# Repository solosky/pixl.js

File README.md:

# Pixl.js

这是一个基于原版[Pixl.js](http://www.espruino.com/Pixl.js)的复刻版本，主要的功能是用来模拟Amiibo。

## 图片

## 文档

* [中文文档](docs/zh/README.md)
* [English Documentation](docs/en/README.md)
* [Italian Documentation](docs/it/README.md)

## Credits

* [FlipperZero Firmware](https://github.com/flipperdevices/flipperzero-firmware)
* [mlib](https://github.com/P-p-H-d/mlib)
* [TLSF](https://github.com/mattconte/tlsf)
* [cwalk](https://github.com/likle/cwalk)
* [SPIFFS](https://github.com/pellepl/spiffs)
* [ChameleonUltra](https://github.com/RfidResearchGroup/ChameleonUltra)
* [CH32V003-GameConsole](https://github.com/wagiminator/CH32V003-GameConsole)

## Contribution 

* 特别感谢 @Caleeeeeeeeeeeee 完善的Bootloader。
* 特别感谢 @白橙 制作的外壳。 
* 特别感谢 @impeeza 提供的文档翻译 。

## 讨论群

国内用户可以加入QQ群 109761876 进行交流。

## Office Channel

Where do you find the community?
* [Pixl.js community discord server](https://discord.gg/4mqeQwcAB2)

## 声明

本项目为开源项目，仅为学习研究用途，请勿用于商业用途。 <br />
Amiibo是任天堂的注册商标，NTAG21X为NXP的注册商标。

内置的Amiibo数据库来源分别如下：

* [amiiloop](https://download.amiloop.app/)
* [AmiiboAPI](https://www.amiiboapi.com/)

源代码没有包含任何有任天堂版权的资源（比如相关密钥，Amiibo原始数据等）。

# License

本项目基于GPL 2.0 License发布，使用请遵循License的约定。

* 如果对项目做了修改，需要把改后的源码发布出来
* 发布出来的源码必须要使用相同的License发布

## 提示 

Amiibo无限刷需要网上搜索key_retail.bin文件然后上传到到磁盘根目录后才能使用。

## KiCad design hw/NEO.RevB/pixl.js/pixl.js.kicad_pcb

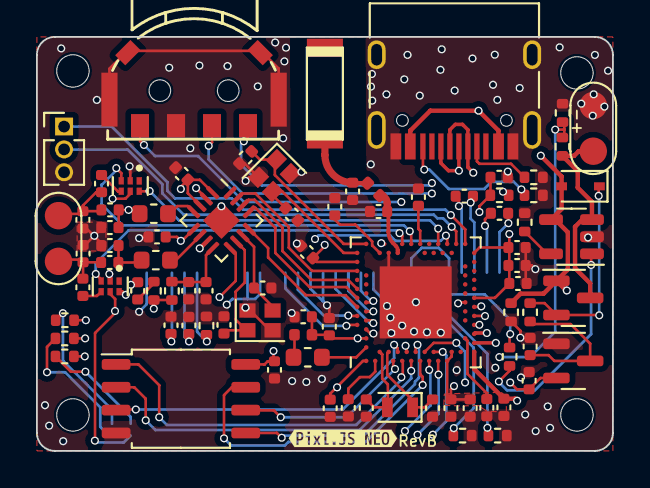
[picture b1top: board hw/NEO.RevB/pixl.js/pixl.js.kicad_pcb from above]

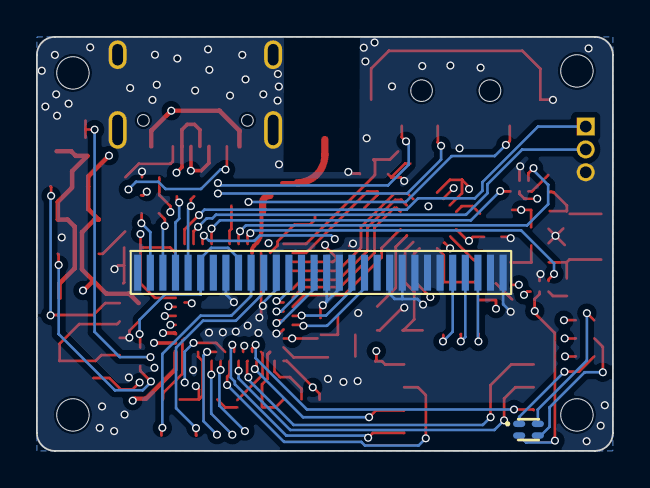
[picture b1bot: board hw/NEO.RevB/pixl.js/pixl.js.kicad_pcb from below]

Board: 4 copper layers, 32.0 x 23.0 mm, 90 parts (2 on the bottom side), 79 nets.

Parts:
BT1: LiPO; NFC_PAD
C1, C6, C13, C14, C17, C20, C24, C28, C30: 0.1uF; C_0402_1005Metric
C2, C5: TBD; C_0402_1005Metric
C3, C4: 15pF; C_0402_1005Metric
C7: 100pF; C_0402_1005Metric
C8, C10, C18, C19, C40: 4.7uF; C_0402_1005Metric
C9: 1nF; C_0402_1005Metric
C11, C21, C25, C29, C33, C36, C37, C42, C43: 1uF; C_0402_1005Metric
C12: 47nF; C_0402_1005Metric
C15, C16, C22, C23: 12pF; C_0402_1005Metric
C26, C27: 22pF; C_0402_1005Metric
C31, C32, C34, C35: 47pF; C_0402_1005Metric
C38, C39: 150pF; C_0402_1005Metric
C41: 2.2uF; C_0402_1005Metric
D1: LED_RGBA; LED-ARRAY-SMD_4P-L1.0-W1.0-TR-RD
D2: 1N5819; D_SOD-323
H1, H2, H3, H4: MountingHole; MountHole_D1.0mm_L10.0mm
J1: SWD; PinHeader_1x03_P1.27mm_Vertical
J2: Conn_01x30; FPC_30P_0.7
L1: TBD; L_0402_1005Metric
L2: 15nH; L_0402_1005Metric
L3: 10uH; L_0603_1608Metric
L4, L5: 2.2uH; L_0603_1608Metric
Q1: AO3401A; SOT-23
R1, R7, R8: 10K; R_0402_1005Metric
R2, R3, R11, R14: 5.1K; R_0402_1005Metric
R4, R5, R6: 1K; R_0402_1005Metric
R9: 806K; R_0402_1005Metric
R10: 2M; R_0402_1005Metric
R12: 100K; R_0402_1005Metric
R13: 0; R_0402_1005Metric
R15: 560K; R_0402_1005Metric
R16, R17: 4.7K; R_0402_1005Metric
U1: Antenna; AN2051
U2: USB_C_Receptacle_USB2.0; USB_C_Receptacle_HRO_TYPE-C-31-M-12
U3: 32MHz; Crystal_SMD_2016-4Pin_2.0x1.6mm
U4: nRF52840; Nordic_AQFN-73-1EP_7x7mm_P0.5mm
U5: 32.768kHz; Crystal_SMD_2012-2Pin_2.0x1.2mm
U6: CI522; QFN-16-1EP_3x3mm_P0.5mm_EP1.45x1.45mm
U7: 27.12MHz; Crystal_SMD_2016-4Pin_2.0x1.6mm
U8: W25Q32JVSS; SOIC-8_5.23x5.23mm_P1.27mm
U9: LTC4054-4.2; TSOT-23-5
U10, U11: 1G3157; PSON50P145X100X60-6N
U12: XC6206P332MR; SOT-23
U13: MSW
U14: NFC Antenna; NFC_PAD
kibuzzard-65881743: G***; kibuzzard-65881743

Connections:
+BATT: BT1.1 (+), Q1.3 (D), R9.1, U9.3 (BAT)
/BAT_ADC: R9.2, R10.1, U4.K2 (AIN3/P0.05)
/CHRG: R7.1, U4.P2 (P1.08), U9.1 (~CHRG)
/COIL_A: C26.1, C34.2, C38.1, U14.1
/COIL_B: C27.1, C35.2, C39.2, U14.2
/HF_CS: U4.A20 (P1.10), U6.15 (NSS)
/HF_MISO: U4.A12 (AIN0/P0.02), U6.12 (MISO)
/HF_MOSI: U4.A14 (P1.15), U6.13 (MOSI)
/HF_SCK: U4.A16 (P1.13), U6.14 (SCK)
/K1: U4.AD8 (P0.13), U13.1
/K2: U4.AD12 (P0.17), U13.T
/K3: U4.AD10 (P0.15), U13.2
/LED_B: R6.1, U4.U1 (TRACEDATA1/P0.12)
/LED_G: R5.1, U4.R1 (TRACEDATA3/P1.09)
/LED_R: R4.1, U4.T2 (TRACEDATA2/P0.11)
/LF_AMP_PWR: U4.W24 (P1.02), U6.2 (NRSTPD)
/NFC_ANT_SEL: U4.U24 (P1.04), U10.6 (S), U11.6 (S)
/NFC_NRF_A: U4.L24 (NFC1/P0.09), U10.3 (B0)
/NFC_NRF_B: U4.J24 (NFC2/P0.10), U11.3 (B0)
/OLED_CS: J2.13, U4.B13 (AIN1/P0.03)
/OLED_DC: J2.15, U4.B9 (AIN6/P0.30)
/OLED_RST: J2.14, U4.B11 (AIN4/P0.28)
/RESET: C1.1, R1.1, U4.AC13 (P0.18/~RESET)
/RX: R11.2, R14.2, U6.9 (RX)
/SPI1_CLK: J2.19, U4.A8 (AIN7/P0.31)
/SPI1_MOSI: J2.18, U4.A10 (AIN5/P0.29)
/SPI2_CLK: U4.G1 (P0.26), U8.6 (CLK)
/SPI2_CS: U4.J1 (AIN2/P0.04), U8.1 (~CS)
/SPI2_IO0: U4.M2 (TRACECLK/P0.07), U8.5 (DI(IO0))
/SPI2_IO1: U4.L1 (P0.06), U8.2 (DO(IO1))
/SPI2_IO2: U4.H2 (P0.27), U8.3 (IO2)
/SPI2_IO3: U4.N1 (P0.08), U8.7 (IO3)
/SWDCLK: J1.2, U4.AA24 (SWDCLK)
/SWDIO: J1.1, U4.AC24 (SWDIO)
/TX1: L4.1, U6.4 (TX1)
/TX2: L5.1, U6.6 (TX2)
/USB_DN: U2.A7 (D-), U2.B7 (D-), U4.AD4 (D-)
/USB_DP: U2.A6 (D+), U2.B6 (D+), U4.AD6 (D+)
/VMID: C25.2, C28.2, R11.1, U6.8 (VMID)
GND: BT1.2 (-), C1.2, C2.2, C3.2, C4.2, C5.2, C6.2, C7.2, C8.2, C9.2, C10.1, C11.1, C12.1, C13.1, C14.1, C15.1, C16.1, C17.1, C18.1, C19.1, C20.1, C21.1, C22.2, C23.2, C24.1, C25.1, C28.1, C29.2, C31.2, C32.1, C33.2, C36.1, C37.1, C38.2, C39.1, C40.1, C41.1, J1.3, J2.1, J2.8, J2.12, J2.16, J2.17, J2.21, J2.22, J2.23, J2.24, J2.25, J2.29, J2.30, R2.1, R3.1, R8.1, R10.2, R12.2, R15.2, R16.2, R17.2, U2.A1 (GND), U2.A12 (GND), U2.B1 (GND), U2.B12 (GND), U2.S1 (SHIELD), U3.2, U3.4, U4.B7 (VSS), U4.EP (VSS), U4.F23 (VSS_PA), U6.17 (VSS), U7.2, U7.4, U8.4 (GND), U9.2 (GND), U10.2 (GND), U11.2 (GND), U12.1 (GND), U13.5, U13.6, U13.7, U13.8, U13.C
unnamed: C30.1, R14.1
unnamed: C30.2, C31.1, C34.1, L4.2
unnamed: C32.2, C35.1, L5.2
unnamed: D1.3 (BK), R6.2
unnamed: D1.2 (GK), R5.2
unnamed: D1.1 (RK), R4.2
unnamed: D2.1 (K), Q1.2 (S), R13.1
unnamed: C42.2, J2.2
unnamed: C42.1, J2.3
unnamed: C43.2, J2.4
unnamed: C43.1, J2.5
unnamed: J2.10, R16.1
unnamed: J2.11, R17.1
unnamed: J2.26, R15.1
unnamed: C40.2, J2.27
unnamed: C41.2, J2.28
unnamed: L2.2, L3.1
unnamed: C2.1, L1.1, U1.1 (A)
unnamed: R2.2, U2.A5 (CC1)
unnamed: R3.2, U2.B5 (CC2)
unnamed: C5.1, L1.2, U4.H23 (ANT)
unnamed: L3.2, U4.B3 (DCC)
unnamed: C6.1, U4.C1 (DEC1)
unnamed: C7.1, U4.D23 (DEC3)
unnamed: C11.2, C12.2, L2.1, U4.B5 (DEC4), U4.E24 (DEC6)
unnamed: C9.1, U4.N24 (DEC5)
unnamed: C8.1, U4.AC5 (DECUSB)
unnamed: C3.1, U3.1, U4.B24 (XC1)
unnamed: C4.1, U3.3, U4.A23 (XC2)
unnamed: C15.2, U4.D2 (XL1/P0.00), U5.2
unnamed: C16.2, U4.F2 (XL2/P0.01), U5.1
unnamed: C22.1, U6.10 (OSCIN), U7.1
unnamed: C23.1, U6.11 (OSCOUT), U7.3
unnamed: R8.2, U9.5 (PROG)
unnamed: C26.2, U10.4 (A)
unnamed: C27.2, U11.4 (A)
unnamed: C29.1, R13.2, U12.3 (VI)
VBUS: C10.2, D2.2 (A), Q1.1 (G), R12.1, U2.A4 (VBUS), U2.A9 (VBUS), U2.B4 (VBUS), U2.B9 (VBUS), U4.AD2 (VBUS), U9.4 (VCC)
VDD: C13.2, C14.2, C17.2, C18.2, C19.2, C20.2, C21.2, C24.2, C33.1, C36.2, C37.2, D1.4 (A), J2.6, J2.9, R1.2, R7.2, U4.A22 (VDD), U4.AD14 (VDD), U4.AD23 (VDD), U4.B1 (VDD), U4.W1 (VDD), U4.Y2 (VDDH), U6.1 (VDD1), U6.3 (VDD2), U6.5 (VDD3), U6.7 (VDD4), U8.8 (VCC), U10.5 (VDD), U11.5 (VDD), U12.2 (VO)

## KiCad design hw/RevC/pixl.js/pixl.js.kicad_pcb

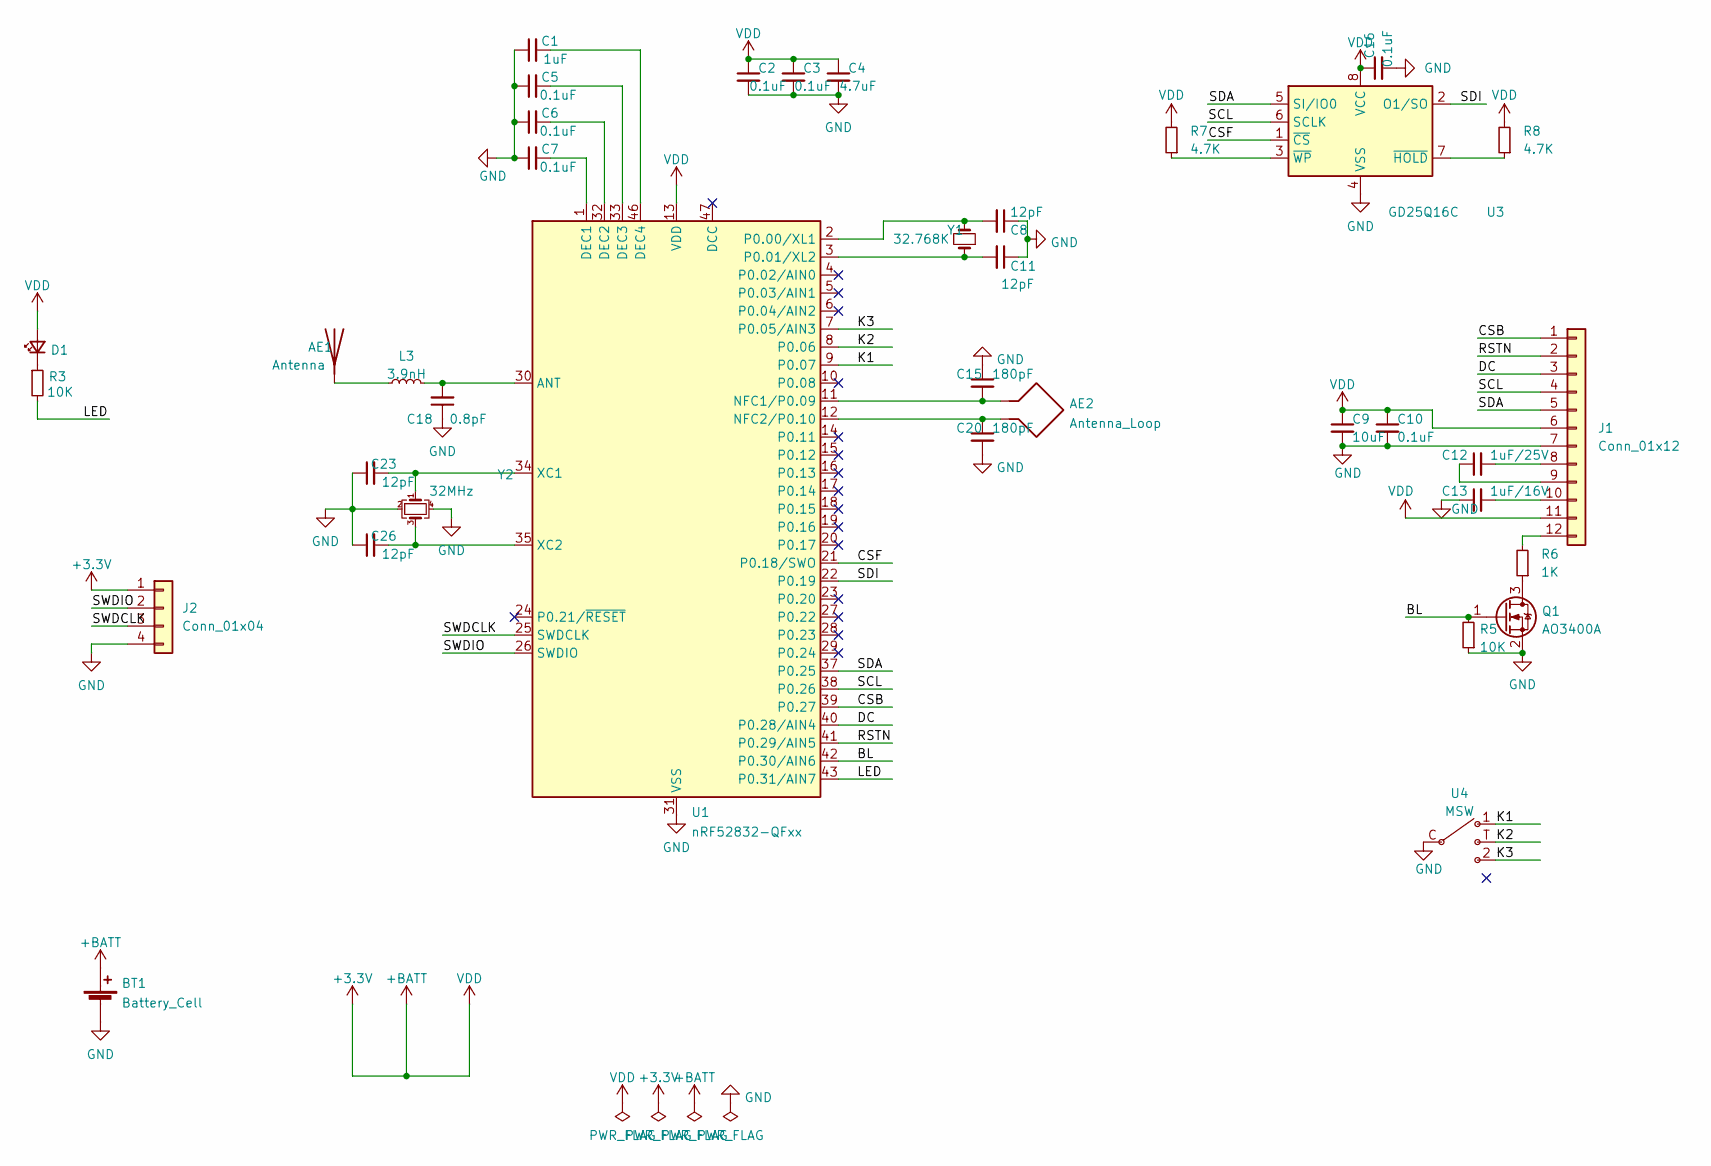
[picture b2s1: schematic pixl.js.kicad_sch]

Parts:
AE1: Antenna; AN2051
AE2: Antenna_Loop; 40x22MM_NFC_ANTENA
BT1: Battery_Cell; BAT-SMD_CR2032-3V
C1: 1uF; C_0402_1005Metric
C2, C3, C5, C6, C7, C10, C16: 0.1uF; C_0402_1005Metric
C4: 4.7uF; C_0402_1005Metric
C8, C11, C23, C26: 12pF; C_0402_1005Metric
C9: 10uF; C_0402_1005Metric
C12: 1uF/25V; C_0402_1005Metric
C13: 1uF/16V; C_0402_1005Metric
C15, C20: 180pF; C_0402_1005Metric
C18: 0.8pF; C_0402_1005Metric
D1: LED_Small; LED_0402_1005Metric
J1: Conn_01x12; FPC_12 0.8mm
J2: Conn_01x04; JST_GH_SM04B-GHS-TB_1x04-1MP_P1.25mm_Horizontal
L3: 3.9nH; L_0402_1005Metric
Q1: AO3400A; SOT-23
R3, R5: 10K; R_0402_1005Metric
R6: 1K; R_0402_1005Metric
R7, R8: 4.7K; R_0402_1005Metric
U1: nRF52832-QFxx; QFN-48-1EP_6x6mm_P0.4mm_EP4.6x4.6mm
U3: GD25Q16C; USON-8_3x2mm_0.5pich
U4: MSW
Y1: 32.768K; Crystal_SMD_2012-2Pin_2.0x1.2mm
Y2: 32MHz; Crystal_SMD_2016-4Pin_2.0x1.6mm

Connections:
+3V3: BT1.1 (+), C2.1, C3.1, C4.1, C9.1, C10.1, C16.1, D1.2 (A), J1.6, J1.11, J2.1, R7.2, R8.2, U1.13 (VDD), U1.36 (VDD), U1.48 (VDD), U3.8 (VCC)
/BL: Q1.1 (G), R5.2, U1.42 (P0.30/AIN6)
/CSB: J1.1, U1.39 (P0.27)
/CSF: U1.21 (P0.18/SWO), U3.1 (~CS)
/DC: J1.3, U1.40 (P0.28/AIN4)
/K1: U1.9 (P0.07), U4.1
/K2: U1.8 (P0.06), U4.T
/K3: U1.7 (P0.05/AIN3), U4.2
/LED: R3.2, U1.43 (P0.31/AIN7)
/RSTN: J1.2, U1.41 (P0.29/AIN5)
/SCL: J1.4, U1.38 (P0.26), U3.6 (SCLK)
/SDA: J1.5, U1.37 (P0.25), U3.5 (SI/IO0)
/SDI: U1.22 (P0.19), U3.2 (O1/SO)
/SWDCLK: J2.3, U1.25 (SWDCLK)
/SWDIO: J2.2, U1.26 (SWDIO)
GND: BT1.2 (-), C1.1, C2.2, C3.2, C4.2, C5.1, C6.1, C7.1, C8.1, C9.2, C10.2, C11.1, C13.1, C15.1, C16.2, C18.1, C20.2, C23.1, C26.1, J1.7, J2.4, Q1.2 (S), R5.1, U1.31 (VSS), U1.45 (VSS), U1.49 (VSS), U3.4 (VSS), U4.C, Y2.2, Y2.4
unnamed: AE1.1 (A), L3.1
unnamed: AE2.1, C15.2, U1.11 (NFC1/P0.09)
unnamed: AE2.2, C20.1, U1.12 (NFC2/P0.10)
unnamed: C1.2, U1.46 (DEC4)
unnamed: C5.2, U1.33 (DEC3)
unnamed: C6.2, U1.32 (DEC2)
unnamed: C7.2, U1.1 (DEC1)
unnamed: C8.2, U1.2 (P0.00/XL1), Y1.2
unnamed: C11.2, U1.3 (P0.01/XL2), Y1.1
unnamed: C12.1, J1.9
unnamed: C12.2, J1.8
unnamed: C13.2, J1.10
unnamed: C18.2, L3.2, U1.30 (ANT)
unnamed: C23.2, U1.34 (XC1), Y2.1
unnamed: C26.2, U1.35 (XC2), Y2.3
unnamed: D1.1 (K), R3.1
unnamed: J1.12, R6.2
unnamed: Q1.3 (D), R6.1
unnamed: R7.1, U3.3 (~WP)
unnamed: R8.1, U3.7 (~HOLD)

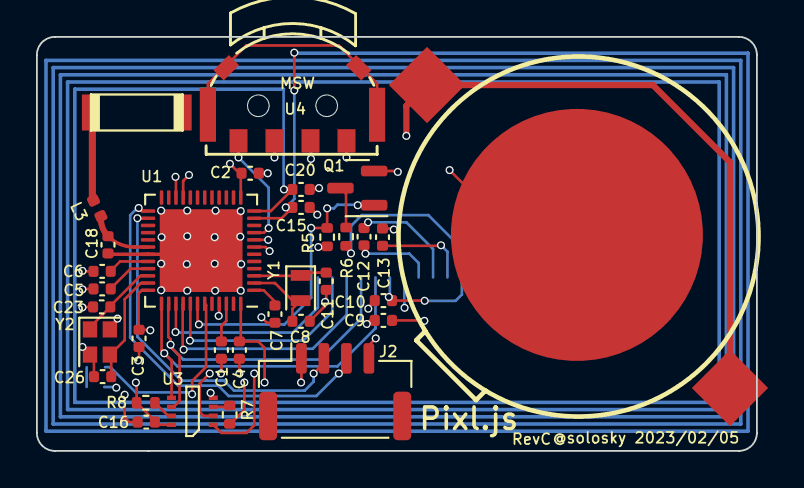
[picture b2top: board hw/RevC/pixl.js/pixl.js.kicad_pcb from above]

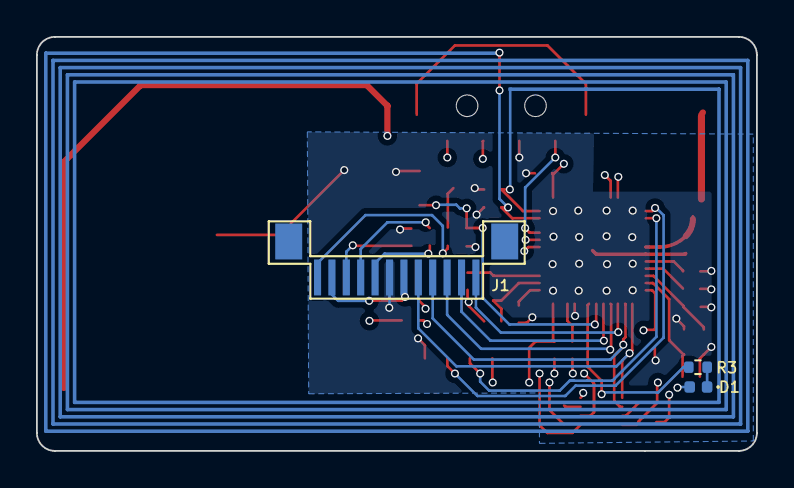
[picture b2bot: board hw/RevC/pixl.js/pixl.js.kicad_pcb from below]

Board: 4 copper layers, 40.0 x 23.0 mm, 37 parts (4 on the bottom side), 36 nets.

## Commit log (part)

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2024-01-22 fixed #207, show confirm box when reset settings
2024-01-22 disable pwm if oled screen
2024-01-23 - replace header CONFIRM with APP_SET_RESET_DEFAULT
2024-01-24 - add uint16_t mui_canvas_draw_utf8_truncate(mui_canvas_t* p_canvas, uint8_t x, uint8_t y, uint8_t max_width, const char *str);
2024-01-24 - optimize code to call mui_canvas_get_utf8_width(p_canvas, getLangString(_L_ELLIPSIS)) only once
2024-01-24 - replace internationalized ellipsis with glyph from u8g2_font_siji_t_6x10
2024-01-27 fix bat
2024-02-04 fix wakeup src check error if sdh is enabled
2024-02-04 fix wrong data length when save card data
2024-02-07 update repair wrong firmware method description
2024-02-14 refactor makefile, support both nrf52840 and nrf53832
2024-02-14 update makefile
2024-02-14 fix build error
2024-02-15 add bootloader LD script
2024-02-16 amiibo_db update
2024-02-17 bl size increase to 36K
2024-02-18 update setting icon
2024-02-20 temp enlarge bl size for testing
2024-02-26 Add files via upload
    添加了部分中文文档
2024-02-26 update docs
2024-03-07 fix bootloader compile error
2024-03-20 Russian translation
2024-03-24 Update Russian language label across locales
    This commit updates the language label for Russian across all language files from English and localized variations to Russian ('Русский'). This change is done to ensure proper language representation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
2024-03-24 enable CI for push request
2024-03-25 change bootloader size to 40KB
2024-03-25 Fix links in 01-Hardware.md
2024-03-26 update bootloader icon
2024-03-29 update firmware build guide
2024-03-29 Update language.h
    added Italian
2024-03-30 changed it_IT language index
2024-03-30 lang IT index moved after last
2024-03-30 prime traduzioni del database amiibo, zelda botw-totk
2024-04-01 tradotti dettagli effetti amiibo su botw e totk
2024-04-02 italian note-it is now used for LANGUAGE_IT_IT
2024-04-02 removed double import and moved to the top
2024-04-02 Update README.md
    added under 文档 link to Italian Documentation
2024-04-02 added full italian docs
2024-04-03 remove duplicate IT_IT declaration
2024-04-03 Add German language to Web App
2024-04-03 Updated Language Files
2024-04-03 Make Font Data Generation script multi-platform
2024-04-03 Update English Translation Guide
2024-04-04 Minor rephrasing for better spacing
2024-04-04 Clarify Random is related to UUID
2024-04-04 remove trailing space for 05+5-translation.md
2024-04-04 add tinyusb submodule
2024-04-05 Port font_data_gen.sh to Python3
2024-04-05 Make font_data_gen.py executable
2024-04-05 Add Linux bdfconv binary (statically linked)
2024-04-05 Fix Path for u8g2_font_wqy12_t_gb2312a.c
2024-04-05 Minor formatting fixes
2024-04-05 Change jp_JP to ja_JP
2024-04-06 Ellipsis typically have 3 dots
2024-04-06 Transfer hard-coded ellipsis to i18n
2024-04-07 Add _L_DELETE_FILE and adjust translations
2024-04-07 Use _T() instead of getLangString()
2024-04-07 Add tinyusb support
2024-04-07 fixed #242: not set correct font when toast draw message
2024-04-09 Add _L_APP_AMIIDB_MORE_MESSAGE
2024-04-09 Optimize de_DE _L_APP_AMIIDB_MORE_MESSAGE
2024-04-09 Add zh_Hans and zh_TW, Fix French _L_KNOW
2024-04-09 Update Font Data
2024-04-10 update web translation docs
2024-04-12 add de language select for en_us
2024-04-14 replacing _L_ON/OFF with _L_ON_F/OFF_F
    where it makes sense. And fixing the translation of the lines “freed” by this in order to more elegantly display what they are left to display now.
2024-04-23 tinyusb port
2024-05-09 English translation improved
2024-05-16 Updated i18n.csv and generated latest en_US.c
2024-05-17 Revised translations
2024-05-18 Put a switch on those things.
2024-06-20 update amiibo database icon, contributed by @baicheng
2024-07-26 update chameleon ultra upstream
2024-07-29 Spnish Translation Tweak
2024-08-11 New tag type select
2024-08-12 Fixed #260: remove deprecated script font_data_gen.sh
2024-08-12 Changes related to commit 877a835
    Russian localization update related to commit 877a835.
2024-08-19 add readonly flag
2024-08-20 amiibo browser and amiidb support read only option #256
2024-08-21 web application supports read only attribute
2024-08-21 add new setting field
2024-08-22 support default card for card emulator app #156
2024-08-23 Changes related to commits 5d4cc1e and 936ef88
    Russian localization update related to commit 5d4cc1e.
    Russian localization update related to commit 936ef88.
2024-08-25 fix card emulator default card
2024-08-26 fix amiibo_db_gen.py
2024-08-28 cu port dev
2024-08-28 add schemetics, PCB and 3d enclosure of pixl.js NEO version
2024-08-29 add front panel project
2024-08-29 upgrade github actions
2024-08-29 update pipelines
2024-09-14 - change glyph in top left corner
2024-09-26 Fixed #281: Add Go Sleep menu in settings
2024-10-13 fix vscode c_cpp_properties.json
2024-10-13 Changes related to commits a1965c7 and 1dd3ec4
    Russian localization update related to commit a1965c7.
    Russian localization update related to commit 1dd3ec4.
2024-10-15 Restoration of lost pt_PT
2024-10-16 Add default interrupt handler to reset device
2024-11-18 add game app
2024-11-19 port game: tiny arkanoid, tiny invaders, tiny tris
2024-11-19 fix sleep issue
2024-11-19 commit 18n.csv
2024-11-20 remove chinese chars to reduce font size
2024-11-20 update board include
2024-11-20 translate game name
2024-11-20 Changes related to commit 9a6c75e
    Russian localization update related to commit 9a6c75e.
2024-11-20 fix screen black issue
2024-11-20 update game app icon
2024-12-24 Renaming an uninitialized card chemeleon card always fails. This change make sure the user will be backed out of the screen when that happens, instead of being permanently stuck on the naming screen.
2025-01-18 Add amiibo series: Super Nintendo World Add new amiibo: Found new amiibo: [000900030432ff02] Diddy Kong - Power Up Band Found new amiibo: [000800030431ff02] Donkey Kong - Power Up Band
2025-01-18 enable contrast menu for LCD model
2025-01-20 Addition of new language values
    Some values where missed on ES translation, here are the missing values.
2025-02-06 disable game app by default to reduce firmware size
2025-02-06 update github actions because of deprecated version of actions/upload-artifact: v3
2025-02-16 add polish translations and new font data
2025-02-24 correction of sequence of translations
    restoration of the historical sequence of appearance/addition of translations, see issue #315
2025-04-13 Add Korean translation
    Added Korean (ko_KR) translations to i18n.csv for improved localization support.
2025-06-07 feat(chameleon): add UID size selection functionality
    - Add new scene for selecting UID size
    - Update existing scenes to support different UID sizes
    - Modify tag helper functions to handle UID size
    - Add translations for new UID size related strings
2025-06-08 Add amiibo: Marisa
2025-06-09 Changes related to commit 88b62d5
    Russian localization update related to commit 88b62d5.
2025-06-10 Remove unrelease card: Marisa
2025-06-12 feat(chameleon): set sak according to tag type when loading data from block0
2025-06-14 fixed #332
2025-06-14 Changes related to commit a905509
    Russian localization update related to commit a905509.
2025-06-14 file EOL fix
2025-06-15 Workaround for issue #336
    Minor Russian translation fix.
2025-06-15 feat(settings): view changes to full screen, fixed #337
2025-06-27 Added swedish web
2025-06-27 i18n script updated strings
2025-06-27 revert of script updating US to SE
2025-06-27 added missing comma
2025-06-27 added Swedish to language picker for web
2025-07-02 fix(i18n): update Spanish translations and fix missing strings
    - Add missing translation for "_L_BYTES" in Spanish
    - Update "_L_APP_AMIIDB_MORE_MESSAGE" and "_L_APP_CHAMELEON_CARD_ADV_LOAD_BLOCK0" translations
    - Fix whitespace and formatting in Spanish locale file
2025-07-02 chore: update submodule dependencies to latest commits
    Update mlib, tlsf, cwalk, spiffs, littlefs, and chameleon-ultra submodules to their latest versions to incorporate upstream improvements and bug fixes
2025-07-22 update amiidb
2025-08-16 add app management menu, app could be disabled or enabled in the desktop #334
2025-08-18 fix: amiibolink button event trigger multiple times
    amiibolink app,进入主菜单时按确认键会触发多次, 表现为在标签主页面按确认会连续进入主菜单页面和模式切换界面.
2025-08-24 update gitignore
2025-09-03 feat: add game list sorting by name and default order in amiidb #344
2025-09-04 feat: add chameleon slot number selection, avaliable slot num are 8, 20, 50 #339
2025-09-07 feat: add slot number setting function and disable unused slots #339
2025-09-07 fix: set minimum OLED contrast to 60 for LCD screens
2025-09-07 fix: set minimum contrast to 60 for LCD screens to prevent invisibility
2025-11-13 Missing nrf_log include + Settings retain logic
2025-11-14 build: add compiler warning flags for pointer and type conversions
    Add specific warning suppression flags to handle incompatible pointer types,
    integer conversions, and implicit function declarations in the build configuration.
2025-11-14 chore: update chameleon-ultra submodule to latest commit
2025-12-04 更新部分MP4 amiibo
2025-12-06 docs: update firmware usage documentation
2025-12-06 fix linker
2025-12-07 fix(amiibo): handle empty chinese name fallback to english
    Check if the Chinese name string is empty before using it as display name, falling back to English name when empty to prevent displaying blank names.
2025-12-07 Added ids and names of two new kirby air rider amiibo
2025-12-07 re-implement get_amiibo_by_id with binary search, now that the amiibo_list is sorted.
2025-12-08 Show settings regardless of app_enable_bits. This presents users from being stuck in a state where settings app is hidden. It could happen due a corrupted or incompatible settings.bin
2025-12-08 Persist the newly generated amiibo upon manual uid regen.
    This is desirable because games like SSB, Splatoon and Kirby Air Riders require stable UIDs. For the generated UIDs to exist only temporariy in RAM doesn't make sense.
2025-12-08 updated amiibo_db_gen.py to sort the amiibo list.
    I ran the script and the generated file was exactly the same as my edits.
    I revert the Kirby amiibo change so make this change more focused.
2025-12-09 refactor(ntag): improve ntag validation and size checking
    - Change `_ntag_data_size` function from inline to static inline for better scope control
    - Add new `is_valid_amiibo_ntag_by_size` helper function to centralize size validation logic
    - Update amiibo detail scene to use new validation function for cleaner code
2025-12-10 Added a bootloader feature to enter DFU by holding stick to RIGHT.
    - The bootloader spins for up to 3 seconds if the user holds the stick to RIGHT at startup.
    - It enters DFU mode when it's still held at the end of that 3 seconds.
    - If the user releases the stick within 3 seconds, it enters application.
2025-12-21 feat(amiibo): add v3 amiibo support and refactor display logic
    - Add new v3 amiibo database and validation checks
    - Implement v3 amiibo generation with proper NTAG_I2C_PLUS_2K format
    - Refactor amiibo display name logic into helper function
    - Update all scenes to use new display name function
    - Add CRC16-MCRF4XX checksum calculation for v3 support
2025-12-24 remove stray log line
2025-12-24 refactor(ntag): centralize ntag type detection logic
    Add _ntag_type helper function to determine tag type based on size
    Update amiidb_api_slot_read and amiibo_scene_amiibo_detail to use new helper
2025-12-24 refactor(amiidb): remove v3 amiibo support and update game db
    - Remove v3 amiibo CSV file and related code
    - Simplify v3 validation check to tail byte comparison
    - Update game database with new entries
    - Remove unused v3 references from header and build files
2026-01-10 update Russian translation (for commit 26b4754)
    Changes related to commit 26b4754 have been made.
2026-01-14 Add Japanese language support to zh_TW.js
